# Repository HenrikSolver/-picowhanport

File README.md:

# Ett enkelt sätt att koppla din nya elmätare till en MQTT broker

## Hårdvara
Koppla ihop en 6 pinnars RJ-12 kontakt med picon enligt följande.

| RJ-12   |RJ- 12| RPI |
|---------|------|-----|
| 1 (Vcc) | 2 (dataReq)    | 39 (VSYS) |
| 5 (data out) | | 7 (UART1 Rx)
| 6 (GND) | | 38 (GND)|

Sätt ett pull upp motstånd på omkring 3 Kohm mellan 7 (UART1 Rx) 36 (3,3V) på pico. Allt enligt nedanstående schema (bidrag från @speedbird620)

## PCB

Ladda upp zipfilen från Gerberfiles mappen till exempelvis https://jlcpcb.com/. 
Om du väljer att använda denna pcb behöver du inte köpa Adapterkort för rj11 kontakt.

## Skal
Om du har en 3D skrivare kolla i stl mappen. Skalet är designat utifrån pcb designen. 

## Mjukvara
Installera micropython och mpremote
* https://micropython.org/download/rp2-pico-w/
* https://docs.micropython.org/en/latest/reference/mpremote.html

Modifiera `config.py`så innehållet passar ditt nätverk.
kopiera `config.py` till picon med `mpremote.py cp config.py :config.py`

Installera paketet umqtt.simple med följande 
```python
import mip
import network
import config

wlan = network.WLAN(network.STA_IF)
wlan.active(True)
wlan.connect(config.SSID, config.PSK)

mip.install("umqtt.simple")
```

kopiera `boot.py` och `main.py` till picon med mpremote

Koppla in picon till din elmätares HAN port med en rak (alltså pin 1 går till pin 1 o.s.v) RJ-12 kabel. LED'en blinkar med omkring 2 Hz medan picon försöker koppla sig till WLAN. När den är uppkopplad lyser den med ett fast sken men släcks en kort stund för varje gång den får data från elmätaren som skickas till MQTT brokern. Denna släckning skall ske var tionde sekund. Hade det varit en fyr så hade den haft karaktären `Oc 10s`

### komponentlista
Detta är de delar jag använt i bygget, man kan naturligtvis köpa motsvarande någon annanstans. Du behöver också en tång för att klämma modularkontakterna.

* https://www.electrokit.com/produkt/modularkontakt-6-6/
* https://www.electrokit.com/produkt/modularkontakt-6-6-pcb/
* https://www.electrokit.com/produkt/telekabel-6x-0-08mm%c2%b2-platt-vit-m/
* https://www.electrokit.com/produkt/raspberry-pi-pico-w/
* https://www.electrokit.com/produkt/metallfilmsmotstand-0-25w-3-01kohm-1-3k01/
  
Om du väljer att använda PCB filerna behöver du inte köpa "Adapterkort för rj11 kontakt".
* https://www.electrokit.com/produkt/adapterkort-for-rj11-kontakt-2-pack/

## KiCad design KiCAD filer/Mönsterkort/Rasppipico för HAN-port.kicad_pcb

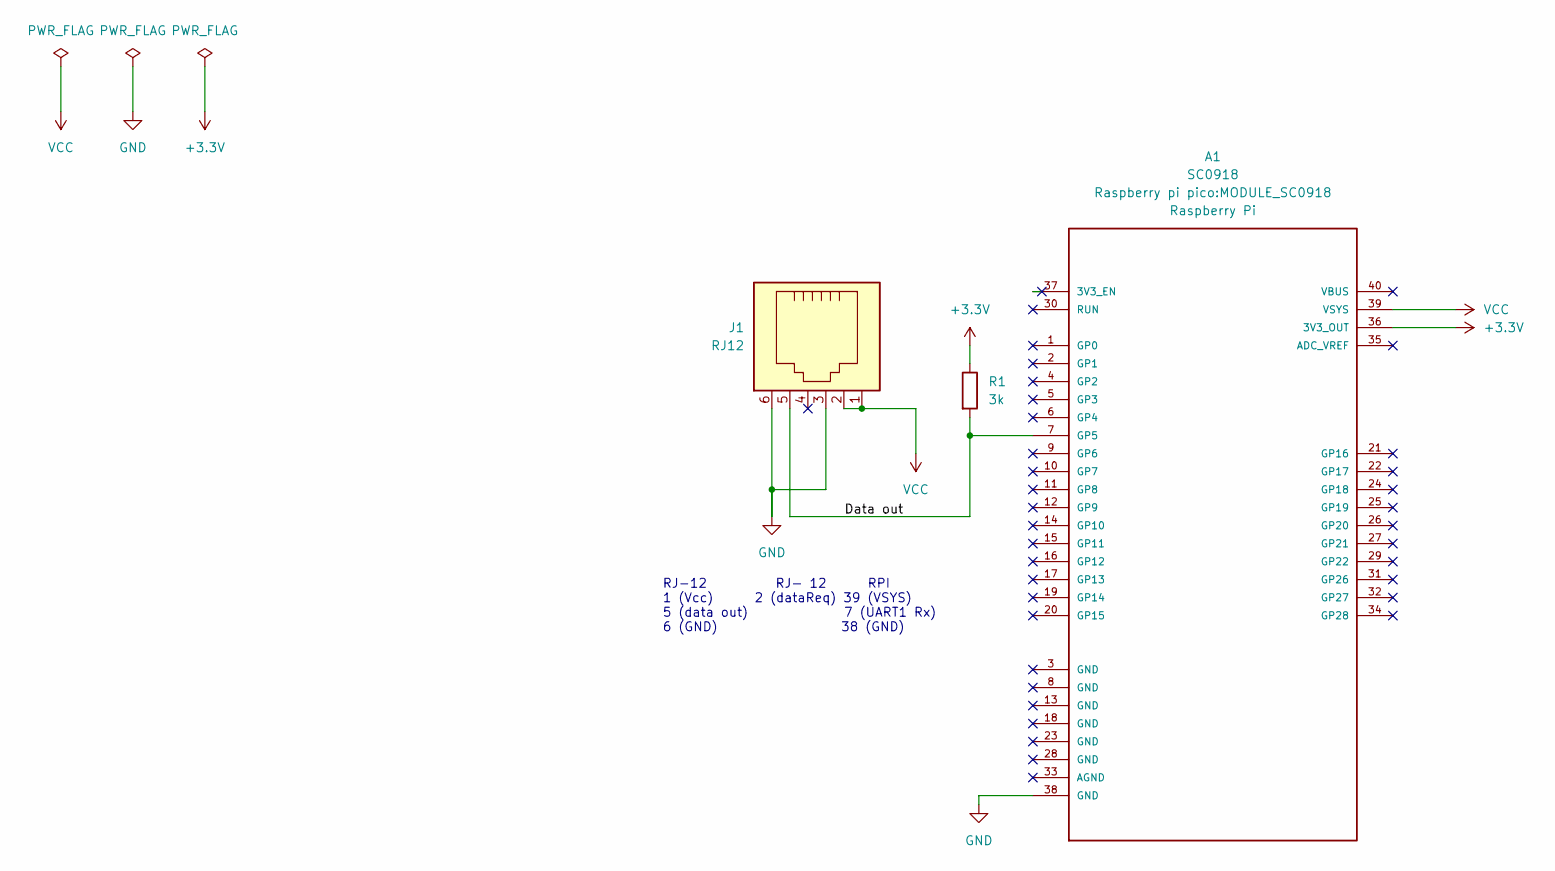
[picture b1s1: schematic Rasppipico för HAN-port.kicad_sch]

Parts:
A1: SC0918; MODULE_SC0918; PARTREV 1.6
J1: RJ12; RJ12_Amphenol_54601-x06_Horizontal1
R1: 3k; R_Axial_DIN0207_L6.3mm_D2.5mm_P10.16mm_Horizontal

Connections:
+3.3V: A1.36 (3V3_OUT), R1.1
/Data out: A1.7 (GP5), J1.5, R1.2
GND: A1.38 (GND), J1.3, J1.6
VCC: A1.39 (VSYS), J1.1, J1.2

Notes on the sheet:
RJ-12 RJ- 12 RPI 1 (Vcc) 2 (dataReq) 39 (VSYS) 5 (data out) 7 (UART1 Rx) 6 (GND) 38 (GND)

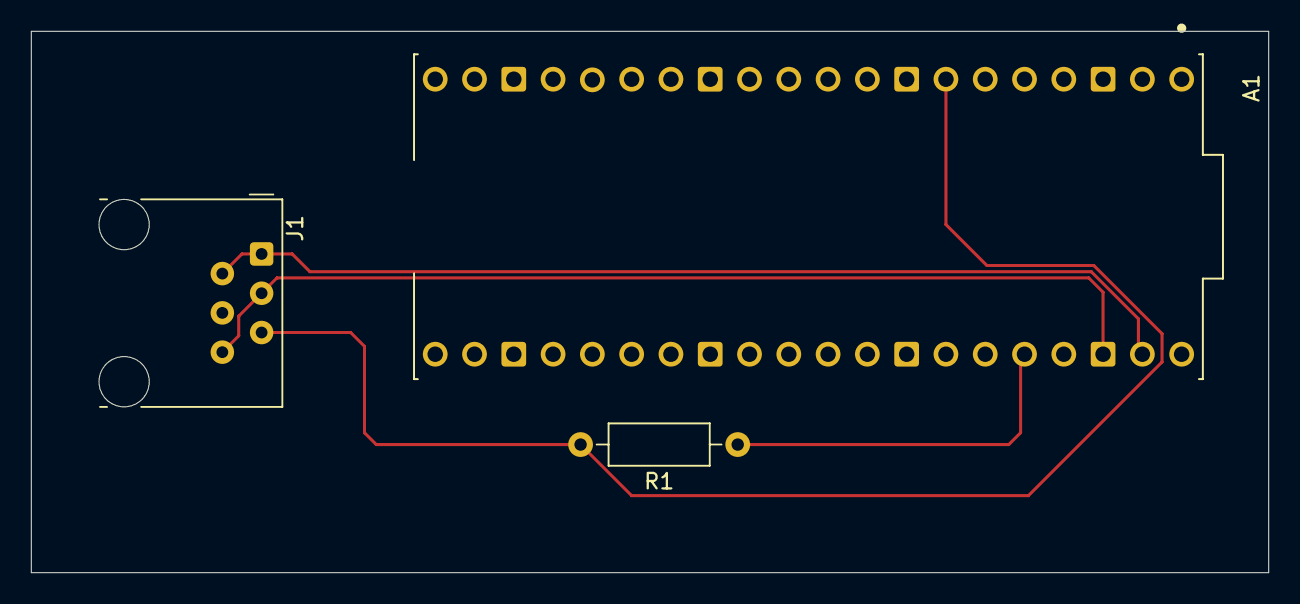
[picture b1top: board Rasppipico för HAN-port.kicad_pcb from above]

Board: 2 copper layers, 80.0 x 35.0 mm, 3 parts (0 on the bottom side), 4 nets.

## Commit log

2024-03-29 data value fix for decimals below 1.00000
2024-03-30 adding obis units
2024-06-17 KiCAD filer
    Innehåller PCB designen och kretsschemat.
2024-06-17 Filer för PCB tillverkning
    De filer som krävs för att kretskort av JLCPCB. Filerna finns även zippade. för enkel uppladdning.
2024-06-17 3D rendering av PCB
2024-06-17 Update README.md
    Information gällande PCB.
2024-06-17 Updaterar filer för PCB.
    Fixade storleken på motståndet.
2024-06-17 Uppdatering av filer och la till stl filer
